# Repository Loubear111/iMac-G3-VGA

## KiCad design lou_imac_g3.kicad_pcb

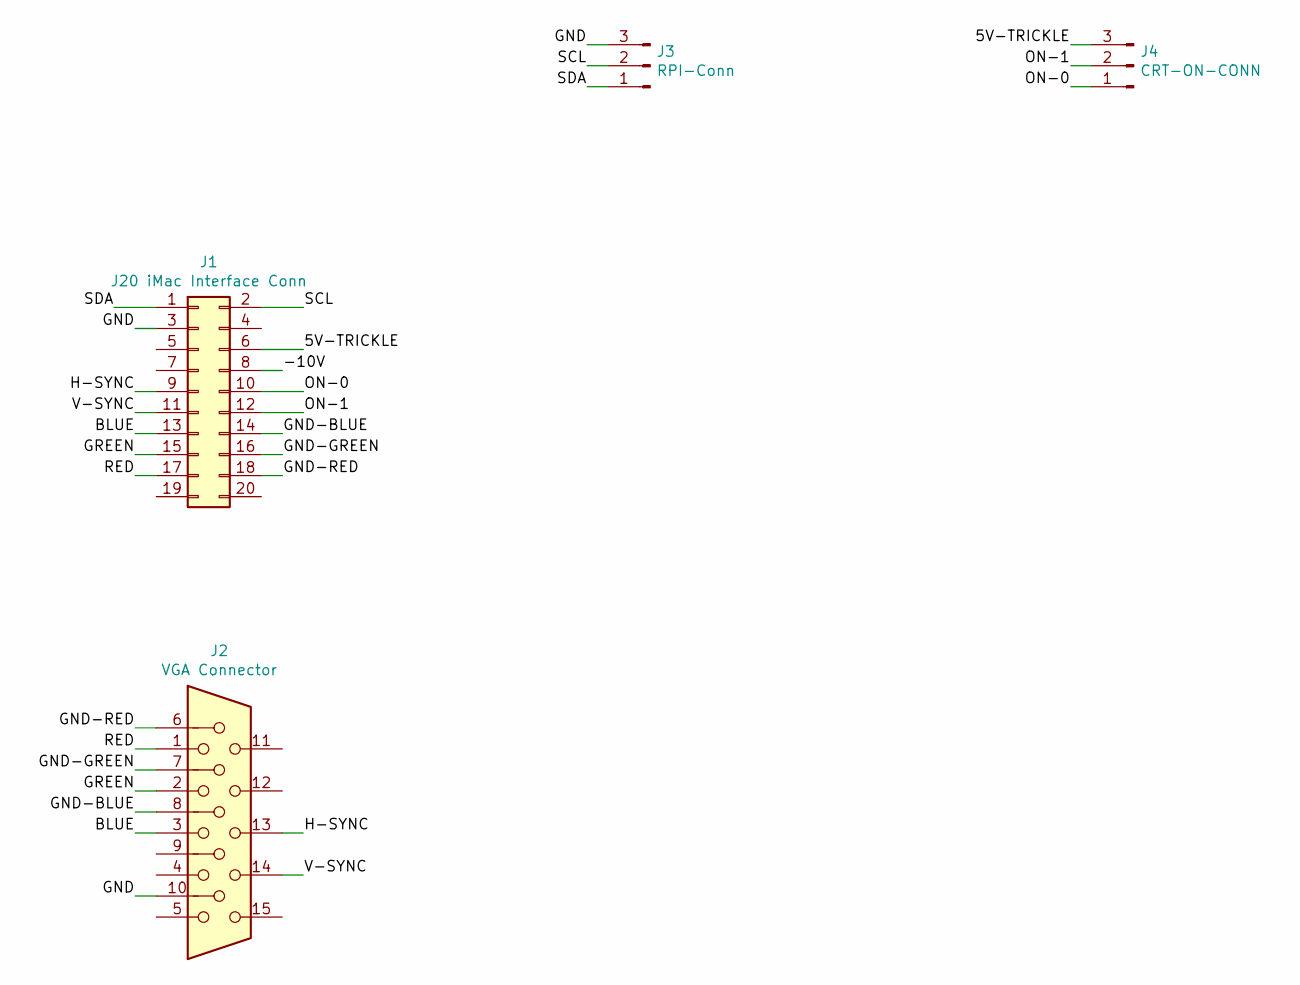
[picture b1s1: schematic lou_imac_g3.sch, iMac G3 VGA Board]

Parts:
J1: J20 iMac Interface Conn; PinHeader_2x10_P2.54mm_Vertical
J2: VGA Connector; DSUB-15-HD_Female_Horizontal_P2.29x1.98mm_EdgePinOffset8.35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
J3: RPI-Conn; PinHeader_1x03_P2.54mm_Vertical
J4: CRT-ON-CONN; PinHeader_1x03_P2.54mm_Vertical

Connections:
/5V-TRICKLE: J1.6, J4.3
/-10V: J1.8
/BLUE: J1.13, J2.3
/GND: J1.3, J2.10, J3.3
/GND-BLUE: J1.14, J2.8
/GND-GREEN: J1.16, J2.7
/GND-RED: J1.18, J2.6
/GREEN: J1.15, J2.2
/H-SYNC: J1.9, J2.13
/ON-0: J1.10, J4.1
/ON-1: J1.12, J4.2
/RED: J1.17, J2.1
/SCL: J1.2, J3.2
/SDA: J1.1, J3.1
/V-SYNC: J1.11, J2.14

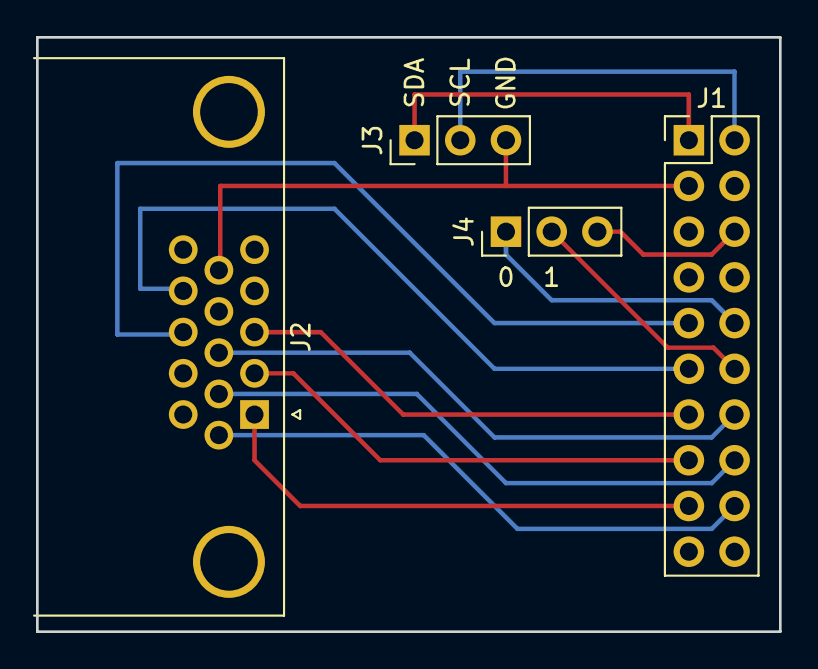
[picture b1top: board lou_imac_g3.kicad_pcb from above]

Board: 2 copper layers, 41.3 x 33.0 mm, 4 parts (0 on the bottom side), 14 nets.

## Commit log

2021-11-21 Initial commit of Rev 1 board files
2021-11-21 Create LICENSE
